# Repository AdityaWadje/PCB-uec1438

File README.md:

# PCB-uec1438
Aditya Wadje ID-2022UEC1438

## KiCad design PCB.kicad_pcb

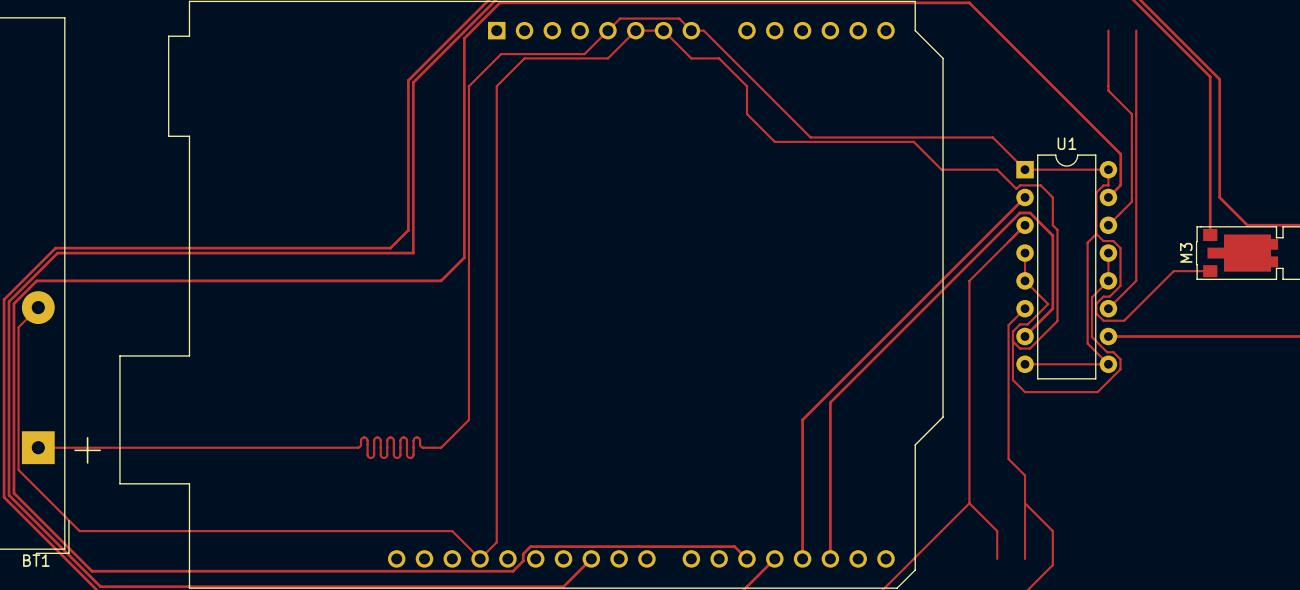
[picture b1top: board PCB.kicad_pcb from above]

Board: 2 copper layers, 4 parts (0 on the bottom side), 7 nets.

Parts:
A1: Arduino_UNO_R3
BT1: Battery; BatteryHolder_TruPower_BH-331P_3xAA
M3: Motor_Servo; Vybronics_VZ30C1T8219732L
U1: L293D; DIP-16_W7.62mm

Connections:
BAT1+: A1.5 (+5V), A1.8 (VIN), BT1.1 (+), M3.1 (PWM), U1.1 (EN1,2), U1.8 (VCC2), U1.9 (EN3,4), U1.16 (VCC1)
BAT1-: A1.6 (GND), A1.7 (GND), A1.29 (GND), BT1.2 (-), U1.4 (GND), U1.5 (GND), U1.12 (GND), U1.13 (GND)
unnamed: A1.25 (D10), M3.2 (+)
U1_D2: A1.17 (D2), U1.7 (2A)
U1_D3: A1.18 (D3), U1.2 (1A)
U1_D4: A1.19 (D4), U1.10 (3A)
U1_D5: A1.20 (D5), U1.15 (4A)
